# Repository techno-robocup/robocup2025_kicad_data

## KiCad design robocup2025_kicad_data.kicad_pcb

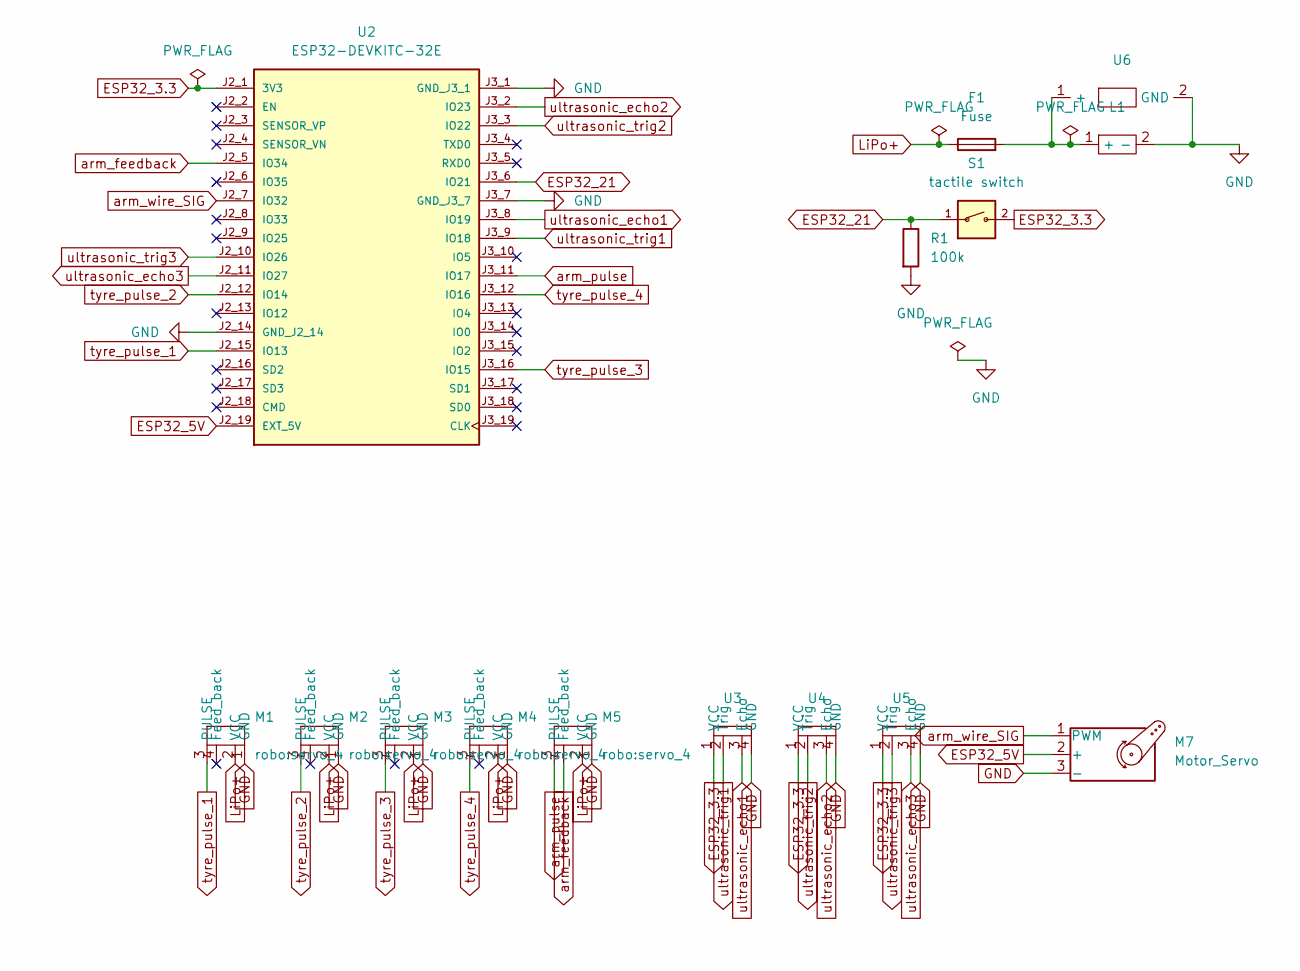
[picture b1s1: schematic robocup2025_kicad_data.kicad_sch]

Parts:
F1: Fuse; fuse_holder
L1: LiPo
M1, M2, M3, M4, M5: servo_4
M7: Motor_Servo; servo_motor_3
R1: 100k; R_Axial_DIN0204_L3.6mm_D1.6mm_P7.62mm_Horizontal
S1: tactile switch; DS-850K-S-ON; PARTREV P6
U2: ESP32-DEVKITC-32E; MODULE_ESP32-DEVKITC-32E; PARTREV 1.4
U3, U4, U5: ultrasonic
U6: voltmeter

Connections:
ESP32_3.3: S1.2, U2.J2_1 (3V3), U3.1 (VCC), U4.1 (VCC), U5.1 (VCC)
ESP32_5V: M7.2 (+), U2.J2_19 (EXT_5V)
ESP32_21: R1.1, S1.1, U2.J3_6 (IO21)
GND: L1.2 (-), M1.1 (GND), M2.1 (GND), M3.1 (GND), M4.1 (GND), M5.1 (GND), M7.3 (-), R1.2, U2.J2_14 (GND_J2_14), U2.J3_1 (GND_J3_1), U2.J3_7 (GND_J3_7), U3.4 (GND), U4.4 (GND), U5.4 (GND), U6.2 (GND)
LiPo+: F1.1, M1.2 (VCC), M2.2 (VCC), M3.2 (VCC), M4.2 (VCC), M5.2 (VCC)
unnamed: F1.2, L1.1 (+), U6.1 (+)
arm_feedback: M5.4 (Feed_back), U2.J2_5 (IO34)
arm_pulse: M5.3 (PULSE), U2.J3_11 (IO17)
arm_wire_SIG: M7.1 (PWM), U2.J2_7 (IO32)
tyre_pulse_1: M1.3 (PULSE), U2.J2_15 (IO13)
tyre_pulse_2: M2.3 (PULSE), U2.J2_12 (IO14)
tyre_pulse_3: M3.3 (PULSE), U2.J3_16 (IO15)
tyre_pulse_4: M4.3 (PULSE), U2.J3_12 (IO16)
ultrasonic_echo1: U2.J3_8 (IO19), U3.3 (Echo)
ultrasonic_echo2: U2.J3_2 (IO23), U4.3 (Echo)
ultrasonic_echo3: U2.J2_11 (IO27), U5.3 (Echo)
ultrasonic_trig1: U2.J3_9 (IO18), U3.2 (Trig)
ultrasonic_trig2: U2.J3_3 (IO22), U4.2 (Trig)
ultrasonic_trig3: U2.J2_10 (IO26), U5.2 (Trig)

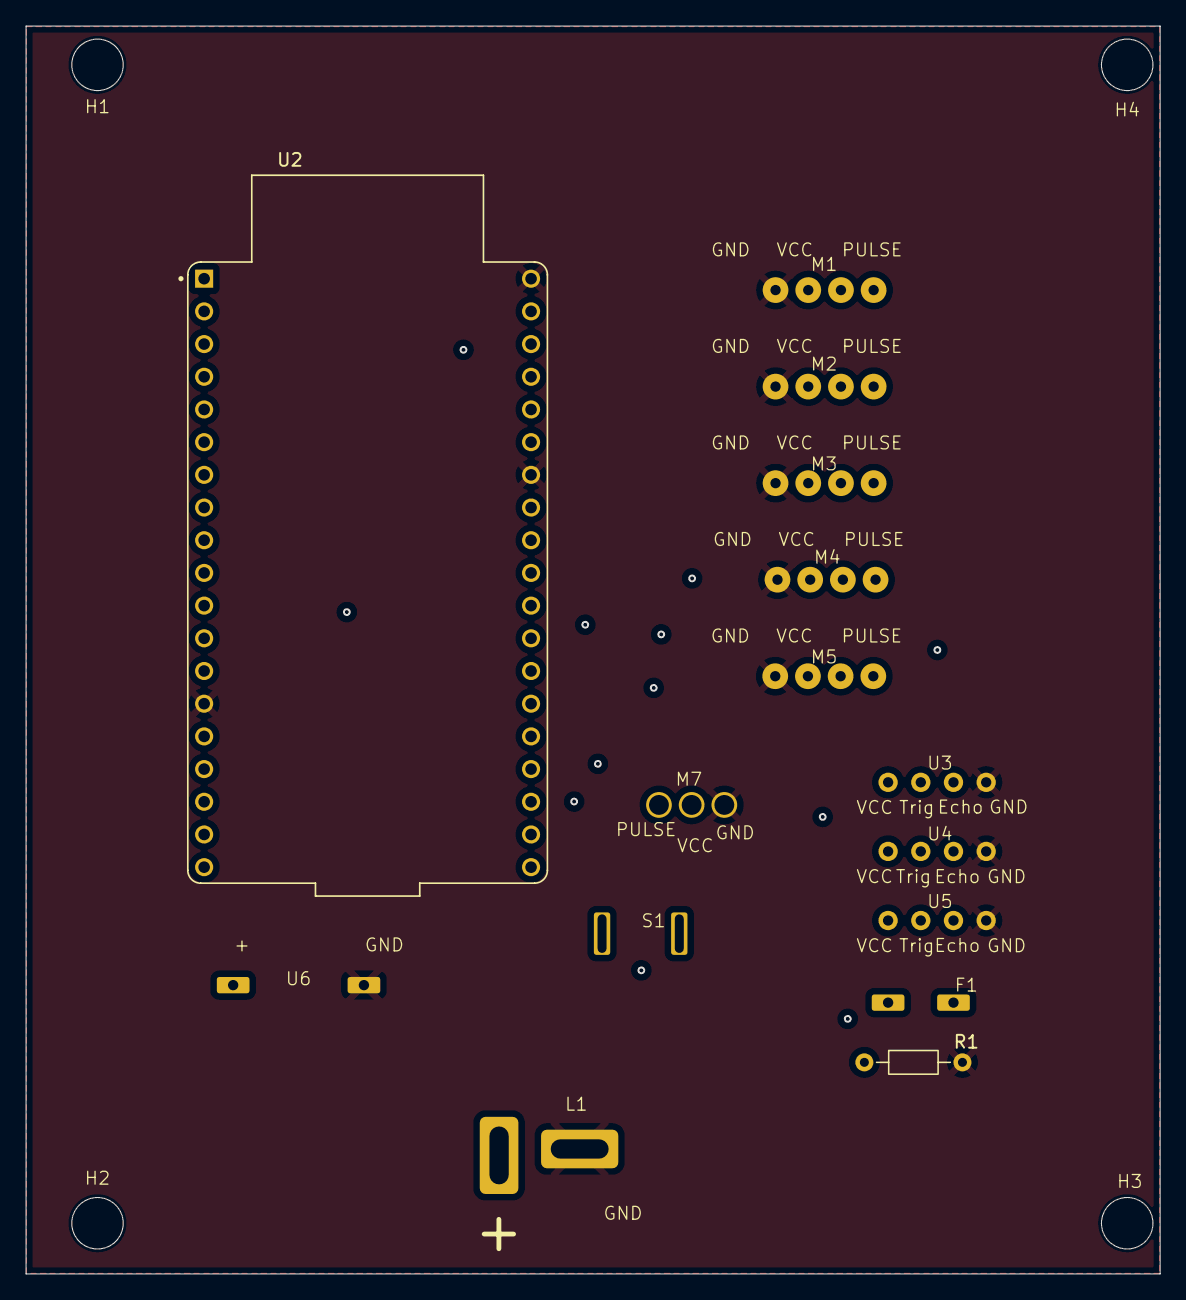
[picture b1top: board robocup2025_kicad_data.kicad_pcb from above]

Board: 4 copper layers, 88.1 x 96.9 mm, 19 parts (0 on the bottom side), 19 nets.

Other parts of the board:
H1, H2, H3, H4: 4mm diameter through hole

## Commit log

2025-04-24 robocup2025_kicad_data.kicad_pcb,robocup2025_kicad_data.kicad_pro robocup2025_kicad_data.kicad_sch: Initialized project
2025-04-24 robocup2025_kicad_data.kicad_prl,robocup2025_kicad_data.kicad_pro robocup2025_kicad_data.kicad_sch: Added i2c pin
2025-04-24 .gitignore: Added gitignore
2025-04-24 robocup2025_kicad_data.kicad_sch: End of the day
    ERC Failing
2025-04-25 robocup2025_kicad_data.kicad_sch: Placed servo motor
2025-04-25 robocup2025_kicad_data.kicad_sch: Created servo motor
2025-04-27 robocup2025_kicad_data.kicad_prl,robocup2025_kicad_data.kicad_pro robocup2025_kicad_data.kicad_sch: Fixed servomotor pin number
2025-04-27 robocup2025_kicad_data.kicad_sch: Connected servo motor to esp
2025-04-27 robocup2025_kicad_data.kicad_sch: Connected ultrasonic sensor
    ERC passing
2025-04-27 robocup2025_kicad_data.kicad_sch: Added footprint for sch
2025-04-27 robocup2025_kicad_data.kicad_pcb,robocup2025_kicad_data.kicad_prl robocup2025_kicad_data.kicad_pro: Placed footprint
2025-04-27 robocup2025_kicad_data.kicad_pcb,robocup2025_kicad_data.kicad_sch: Commit
2025-04-27 robocup2025_kicad_data.kicad_pcb,robocup2025_kicad_data.kicad_prl: Replaced footprint, created cut layer
2025-04-28 robocup2025_kicad_data.kicad_pcb,robocup2025_kicad_data.kicad_prl robocup2025_kicad_data.kicad_pro: Set settings
2025-04-28 robocup2025_kicad_data.kicad_pcb: Edited outline
2025-04-28 robocup2025_kicad_data.kicad_pcb,robocup2025_kicad_data.kicad_prl: Colored layer
2025-04-28 robocup2025_kicad_data.kicad_pcb,robocup2025_kicad_data.kicad_pro: Lined all the stuff
    However, design check failing. The ultrasonic pads are causing the
    trouble
2025-04-28 Save clear data Delete lines.
2025-04-29 make pcb and wiring. with unconnected
2025-04-30 Clear pcb.
2025-04-30 Add wire_servo & ultrasonic sensor
2025-04-30 robocup2025_kicad_data.kicad_sch: Moved place of symbol
2025-04-30 robocup2025_kicad_data.kicad_sch: Added voltmeter in schematics
2025-04-30 robocup2025_kicad_data.kicad_sch: Assigned footprint for voltmeter
2025-04-30 robocup2025_kicad_data.kicad_sch: Remaped servo motor's footprints correctly
2025-04-30 .gitignore: Updated gitignore
2025-04-30 robocup2025_kicad_data.kicad_sch: Modified GND to use default symbol
2025-04-30 robocup2025_kicad_data.kicad_sch: Applied footprint for voltmeter
2025-04-30 robocup2025_kicad_data.kicad_pcb: Brand new pcb
    There are no errors except the missing pin in raspberrypi from S1 ~ S4
2025-04-30 Add PCB
    Unwired
2025-04-30 robocup2025_kicad_data.kicad_sch: Changed to use default sch for simple servo
2025-04-30 Revert "Add PCB"
    This reverts commit 4502c4b60855c347e7909f12c40e53bd4caa44e2.
    Who makes a commit while somebody is editing the file.
2025-04-30 auto_saved_files#,_autosave-robocup2025_kicad_data.kicad_sch robocup2025_kicad_data.kicad_sch: Assigned footprint for simple servo motor
2025-04-30 robocup2025_kicad_data.kicad_pcb: Placed copper for front and back layer
2025-04-30 robocup2025_kicad_data.kicad_pcb: Replaced parts
2025-04-30 robocup2025_kicad_data.kicad_pcb,robocup2025_kicad_data.kicad_prl: Painted solid
2025-04-30 robocup2025_kicad_data.kicad_pcb,robocup2025_kicad_data.kicad_prl: Great, all done for now!
    No errors
2025-04-30 robocup2025_kicad_data.kicad_pcb,robocup2025_kicad_data.kicad_prl: Great
2025-05-09 add: Added discord notification on commit
2025-05-23 Create LICENSE
2025-05-24 rm: Removed raspberrypi object
2025-05-24 add: Added fuse and cleaned schematics
2025-05-24 assigned footprint for fuse in schematics
    #5
2025-05-24 fixed schematics, erc passing
    #5
2025-05-24 placed items in pcb
2025-05-26 removed sda and scl
    erc passing
2025-05-26 replaced items
2025-05-26 added switch
2025-05-26 placed
2025-05-30 fix: Made the pin "non-floating"
2025-06-06 Fix sch data
    Edit ultra sonic's pin
2025-06-06 updated schematics
2025-06-09 updated sch
    assigned footprint for resistor
2025-06-09 updated pcb
2025-06-09 updated footprint
    fixed fuse
2025-06-09 replaced all objects
2025-06-09 changed place
2025-06-09 new edge on pcb
2025-06-09 created through hole
2025-06-09 removed 2mm throughhole
2025-06-09 I do not know what happened
2025-06-09 placed 4mm through hole
2025-06-09 filled gnd and lipo
2025-06-09 changed reference
2025-06-10 pcb done!
2025-06-10 Done!!
2025-06-10 Done!!!
2025-06-10 Done!!!!
2025-06-21 removed all lines and vias
2025-06-28 replaced all the items on pcb
2025-06-28 filled all the f.cu and b.cu
2025-06-28 routed all parts
    DRC passing
2025-06-29 made production
2025-06-29 `fabrication-toolkit-options.json` added
2025-07-07 fixed size of the button
2025-07-17 clean
2025-07-17 Lipo and GND
2025-07-17 fixed
2025-07-17 done
2025-08-30 Added value of resistor
2025-09-14 Modified pcb's and schematics
    Modifying the footprints of the big servo to be able
    to connect from pin headers.
    Modifying the schematics and pcb's for wire servo
    to use 5V instead of LiPo.
    Modifying the pcb's lines from 2.0mm to 0.2mm.
2025-09-14 Removed tracks
2025-09-14 0.2mm to 2.0mm
2025-09-14 Update production
